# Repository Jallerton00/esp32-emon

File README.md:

# esp32-emon

A simple energy monitor based off early versions of an energy monitor by openenergymonitor.org.

## Hardware

[PDF Schematic](/hardware/esp32-emon/schematic.pdf)

## Software

The software uses [EmonLib](https://github.com/openenergymonitor/EmonLib) and integrates with HomeAssistant through [ESPHome](https://esphome.io/index.html).

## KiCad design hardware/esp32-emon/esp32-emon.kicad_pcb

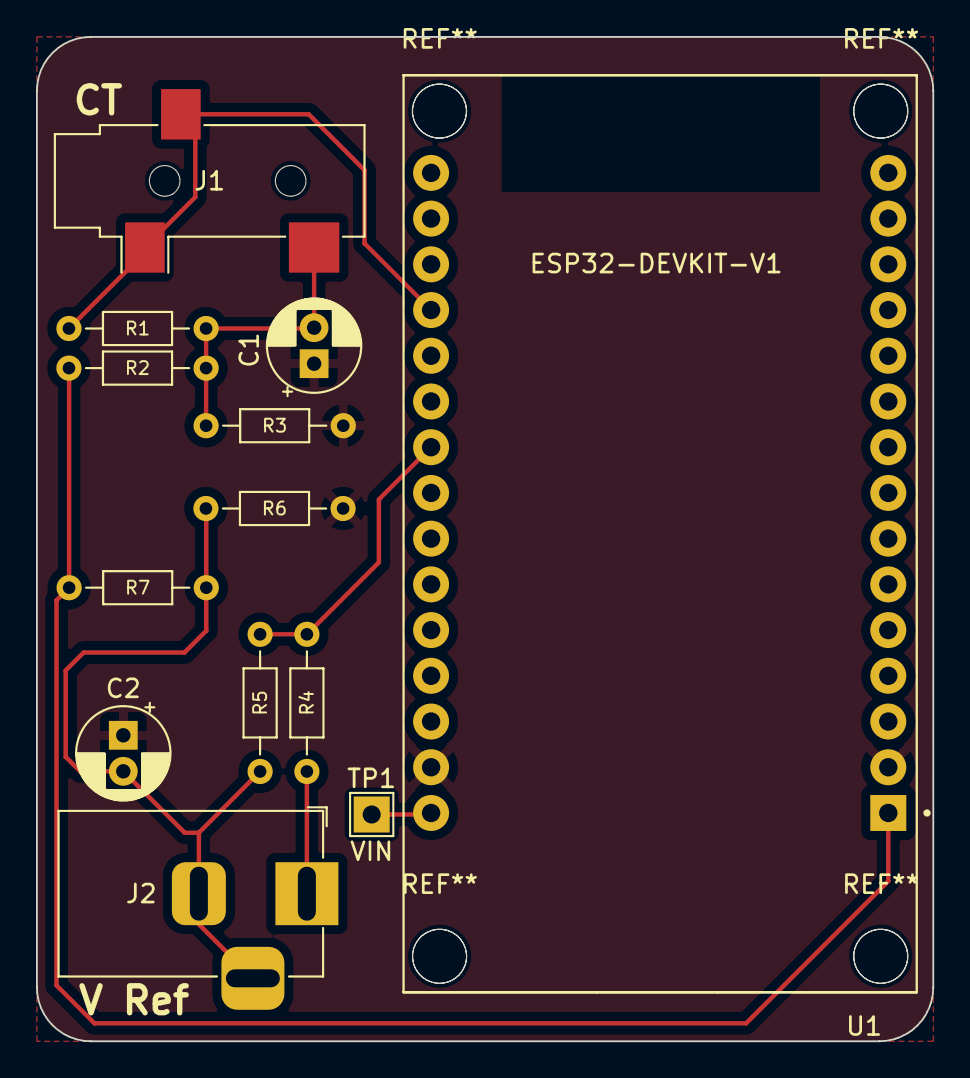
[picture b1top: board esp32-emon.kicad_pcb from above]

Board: 2 copper layers, 49.8 x 55.8 mm, 13 parts (0 on the bottom side), 8 nets.

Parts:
C1, C2: 10uF; CP_Radial_D5.0mm_P2.00mm
J1: SJ-3523-SMT-TR; Jack_3.5mm_CUI_SJ-3523-SMT_Horizontal
J2: Barrel_Jack; BarrelJack_Horizontal
R1: 18R; R_Axial_DIN0204_L3.6mm_D1.6mm_P7.62mm_Horizontal
R2, R3, R6, R7: 470K; R_Axial_DIN0204_L3.6mm_D1.6mm_P7.62mm_Horizontal
R4: 100K; R_Axial_DIN0204_L3.6mm_D1.6mm_P7.62mm_Horizontal
R5: 10K; R_Axial_DIN0204_L3.6mm_D1.6mm_P7.62mm_Horizontal
TP1: VIN; TestPoint_THTPad_2.0x2.0mm_Drill1.0mm
U1: ESP32-DEVKIT-V1; MODULE_ESP32_DEVKIT_V1

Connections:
+3V3: R2.1, R7.1, U1.1 (3V3)
/ADC1 CH5: R4.1, R5.2, U1.22 (D33)
/ADC1 CH6: J1.R, J1.S, R1.2, U1.19 (D34)
GND: C1.1, C2.1, R3.2, R6.1, U1.2 (GND), U1.29 (GND)
unnamed: C1.2, J1.T, R1.1, R2.2, R3.1
unnamed: C2.2, J2.2, J2.3, R5.1, R6.2, R7.2
unnamed: J2.1, R4.2
unnamed: TP1.1, U1.30 (VIN)

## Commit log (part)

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2023-05-01 Remove backup dir
2023-05-01 Add code from greatscott and add emonlib as a submodule
2023-05-01 Updates for v0.1
2023-05-01 v0.1 order
2023-05-01 Add 3d models
2023-05-03 Initial working voltage
2023-05-03 Update from 1K to 10K
2023-05-03 Update calibration for new resistors
2023-05-03 Change update interval to 1s
2023-05-05 Add secrets for encryption and OTA
2023-05-15 Calibrate (roughly) after PCB installation
2023-05-15 Add device classes and manage sensor units from custom integration (rather than YAML)
2024-05-05 Update images, schematic and gerbers
2024-05-05 Add README
2024-05-05 Update main.yaml and remove old manufacture files
2024-05-05 Update automation to only run on HW change
2024-05-05 Add ability to run automation manually
2024-06-19 Test TurboCase
